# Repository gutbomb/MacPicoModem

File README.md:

# Mac Pico Modem

## A Pico W based RS422 \<-\> WiFi modem with Hayes AT style commands and Global Village Teleport style LED indicators

| The Mac Pico modem |

This project is an adaptation of the [mecparts](https://github.com/mecparts)'s 
[Pico WiFi Modem](https://github.com/mecparts/PicoWiFiModem). 

My goal was to make it work with a mac serial port, look the part, and be
cheaper to make.

### First time setup

The default serial configuration is 9600bps, 8 data bits, no parity, 1
stop bit.

Here's the commands you need to set up the modem to automatically
connect to your WiFi network:

1. `AT$SSID=your WiFi network name` to set the WiFi network that the
modem will connect to when it powers up.
2. `AT$PASS=your WiFi network password` to set the password for the
network.
3. `ATC1` to connect to the network.
4. Optional stuff:
   * `AT$SB=speed` to set the default serial speed.
   * `AT$SU=dps` to set the data bits, parity and stop bits.
   * `ATNETn` to select whether or not to use Telnet protocol.
   * `AT&Kn` to use RTS/CTS flow control or not.
   * `AT&Dn` to set up DTR handling.
5. `AT&W` to save the settings.

Once you've done that, the modem will automatically connect to your WiFi
network on power up and will be ready to "dial up" a connection with
ATDT.

### Command Reference

Multiple AT commands can be typed in on a single line. Spaces between
commands are allowed, but not within commands (i.e. AT S0=1 X1 Q0 is
fine; ATS 0=  1 is not). Commands that take a string as an argument
(e.g. AT$SSID=, AT$TTY=) assume that *everything* that follows is a part
of the string, so no commands are allowed after them.

Command | Details
------- | -------
+++     | Online escape code. Once your modem is connected to another device, the only command it recognises is an escape code of a one second pause followed by three typed plus signs and another one second pause, which puts the modem back into local command mode.
A/      | Repeats the last command entered. Do not type AT or press Enter.
AT      | The attention prefix that precedes all command except A/ and +++.
AT?     | Displays a help cheatsheet.
ATA     | Force the modem to answer an incoming connection when the conditions for auto answer have not been satisfied.
ATC?<br>ATC*n* | Query or change the current WiFi connection status. A result of 0 means that the modem is not connected to WiFi, 1 means the modem is connected. The command ATC0 disconnects the modem from a WiFi connection. ATC1 connects the modem to the WiFi.
ATDS*n* | Calls the host specified in speed dial slot *n* (0-9).
ATDT<i>[+=-]host[:port]</i> | Tries to establish a WiFi TCP connection to the specified host name or IP address. If no port number is given, 23 (Telnet) is assumed. You can also use ATDT to dial one of the speed dial slots in one of two ways:<br><br><ul><li>The alias in each speed dial slot is checked to see if it matches the specified hostname.</li><li>A host specified as 7 identical digits dials the slot indicated by the digit. (i.e. 2222222 would speed dial the host in slot 2).</li></ul>Preceding the host name or IP address with a +, = or - character overrides the ATNET setting for the period of the connection.<br><br><ul><li>**+** forces NET2 (fake Telnet)</li><li>**=** forces NET1 (real Telnet)</li><li>**-** forces NET0 (no Telnet)</li></ul>Once the dial attempt has begun, pressing any key before the connection is established will abort the attempt.
ATE?<br>ATE*n* | Command mode echo. Enables or disables the display of your typed commands.<br><br><ul><li>E0 Command mode echo OFF. Your typing will not appear on the screen.</li><li>E1 Command mode echo ON. Your typing will appear on the screen.</li></ul>
ATGET*http&#58;//host[/page]* | Displays the contents of a website page. **https** connections are not supported. Once the contents have been displayed, the connection will automatically terminate.
ATH | Hangs up (ends) the current connection.
ATI | Displays the current network status, including sketch build date, WiFi and call connection state, SSID name, IP address, and bytes transferred.
ATNET?<br>ATNET*n* | Query or change whether telnet protocol is enabled. A result of 0 means that telnet protocol is disabled; 1 is *Real* telnet protocol and 2 is *Fake* telnet protocol. If you are connecting to a telnet server, it may expect the modem to respond to various telnet commands, such as terminal name (set with `AT$TTY`), terminal window size (set with `AT$TTS`) or terminal speed. Telnet protocol should be enabled for these sites, or you will at best see occasional garbage characters on your screen, or at worst the connection may fail.<br><br>The difference between *real* and *fake* telnet protocol is this: with *real* telnet protocol, a carriage return (CR) character being sent from the modem to the telnet server always has a NUL character added after it. The implementation of the telnet protocol used by some BBSes doesn't properly strip out the NUL character. When connecting to such BBSes (Particles! is one), use *fake* telnet.<br><br>When using *real* telnet protocol, when the telnet server sends a CR character followed by a NUL character, only the CR character will be sent to the serial port; the NUL character will be silently stripped out. With *fake* telnet protocol, the NUL will be passed through.
ATO | Return online. Use with the escape code (+++) to toggle between command and online modes.
ATQ?<br>ATQ*n* | Enable or disable the display of result codes. The default is Q0.<br><br><ul><li>Q0 Display result codes.</li><li>Q1 Suppress result codes (quiet).</li></ul>
ATRD<br>ATRT | Displays the current UTC date and time from NIST in the format *YY-MM-DD HH:MM:SS*. A WiFi connection is required and you cannot be connected to another site.
ATS0?<br>ATS0=*n* | Display or set the number of "rings" before answering an incoming connection. Setting `S0=0` means "don't answer".
ATS2?<br>ATS2=*n* | Display or set the ASCII code used in the online escape sequence. The default value is 43 (the + plus character). Setting it to any value between 128 and 255 will disable the online escape function.
ATV?<br>ATV*n* | Display result codes in words or numbers. The default is V1.<br><br><ul><li>V0 Display result codes in numeric form.</li><li>V1 Display result codes in text form.</li></ul>
ATX?<br>ATX*n* | Control the amount of information displayed in the result codes. The default is X1 (extended codes).<br><br><ul><li>X0 Display basic codes (CONNECT, NO CARRIER)</li><li>X1 Display extended codes (CONNECT speed, NO CARRIER (connect time))</li></ul>
ATZ | Resets the modem.
AT&D?<br>AT&D*n* | Display or set the handling of DTR going inactive. The default is &D0 (ignored).<br><br><ul><li>&D0 Ignore</li><li>&D1 Go to command mode</li><li>&D2 End call</li><li>&D3 Reset modem</li></ul>
AT&F | Reset the NVRAM contents and current settings to the sketch defaults. All settings, including SSID name, password and speed dial slots are affected.
AT&K?<br>AT&K*n* | Data flow control. Prevents the modem's buffers for received and transmitted from overflowing.<br><br><ul><li>&K0 Disable data flow control.</li><li>&K1 Use hardware flow control. Requires that your computer and software support Clear to Send (CTS) and Request to Send (RTS) at the RS-232 interface.</li></ul>
AT&R?<br>AT&R=*server pwd* | Query or change the password for incoming connections. If set, the user has 3 chances in 60 seconds to enter the correct password or the modem will end the connection.
AT&V*n* | Display current or stored settings.<br><br><ul><li>&V0 Display current settings.</li><li>&V1 Display stored settings.</li></ul>
AT&W | Save current settings to NVRAM.
AT&Zn?<br>AT&Z*n*=*host[:port],alias* | Store up to 10 numbers in NVRAM, where *n* is the position 0-9 in NVRAM, and *host[:port]* is the host string, and *alias* is the speed dial alias name. The host string may be up to 50 characters long, and the alias string may be up to 16 characters long.<br><br>Example: `AT&Z2=particlesbbs.dyndns.org:6400,particles`<br><br>This number can then be dialed in any of the following ways:<br><br><ul><li>`ATDS2`</li><li>`ATDTparticles`</li><li>`ATDT2222222`</li></ul>
AT$AE?<br>AT$AE=*startup AT cmd* | Query or change the command line to be executed when the modem starts up.
AT$AYT | Sends a Telnet "Are You There?" command if connected to a Telnet remote.
AT$BM?<br>AT$BM=*server busy msg* | Query or change a message to be returned to an incoming connection if the modem is busy (i.e. already has a connection established).
AT$MDNS<br>AT$MDNS=*mDNS name* | Query or change the mDNS network name (defaults to "espmodem"). When a non zero TCP port is defined, you can telnet to that port with **telnet mdnsname.local port**.
AT$PASS?<br>AT$PASS=*WiFi pwd* | Query or change the current WiFi password. The password is case sensitive. Clear the password by issuing the set command with no password. The maximum length of the password is 64 characters.
AT$SB?<br>AT$SB=*n* | Query or change the current baud rate. Valid values for "n" are 110, 300, 450, 600, 710, 1200, 2400, 4800, 9600, 19200, 38400, 57600, 76800 and 115200. Any other value will return an ERROR message. The default baud rate is 1200. The Pico WiFi modem does not automatically detect baud rate like a dial-up modem. The baud rate setting must match that of your terminal to operate properly. It will display garbage in your terminal otherwise.
AT$SP?<br>AT$SP=*n* | TCP server port to listen on. A value of 0 means that the TCP server is disabled, and no incoming connections are allowed.
AT$SSID?<br>AT$SSID=*ssid name* | Query or change the current SSID to the specified name. The given SSID name is case sensitive. Clear the SSID by issuing the set command with no SSID. The maximum length of the SSID name is 32 characters.
AT$SU?<br>AT$SU=*dps* | Query or change the current number of data bits ('d'), parity ('p') and stop bits ('s") of the serial UART. Valid values for 'd' are 5, 6, 7 or 8 bits. Valid values for 'p' are (N)one, (O)dd or (E)ven parity. Valid values for 's' are 1 or 2 bits. The default settings are 8N1. The UART setting must match your terminal to work properly.
AT$TTL?<br>AT$TTL=*telnet location* | Query or change the Telnet location value to be returned when the Telnet server issues a SEND-LOCATION request. The default value is "Computer Room".
AT$TTS?<br>AT$TTS=*WxH* | Query or change the window size (columns x rows) to be returned when the Telnet server issues a NAWS (Negotiate About Window Size) request. The default value is 80x24. For terminals that are smaller than 80x24, setting these values appropriately will enable paging on the help (AT?) and network status (ATI) commands.
AT$TTY?<br>AT$TTY=*terminal type* | Query or change the terminal type to be returned when the Telnet server issues a TERMINAL-TYPE request. The default value is "ansi".
AT$W?<br>AT$W=*n* | Startup wait.<br><br><ul><li>$W=0 Startup with no wait.</li><li>$W=1 Wait for the return key to be pressed at startup.</li></ul>

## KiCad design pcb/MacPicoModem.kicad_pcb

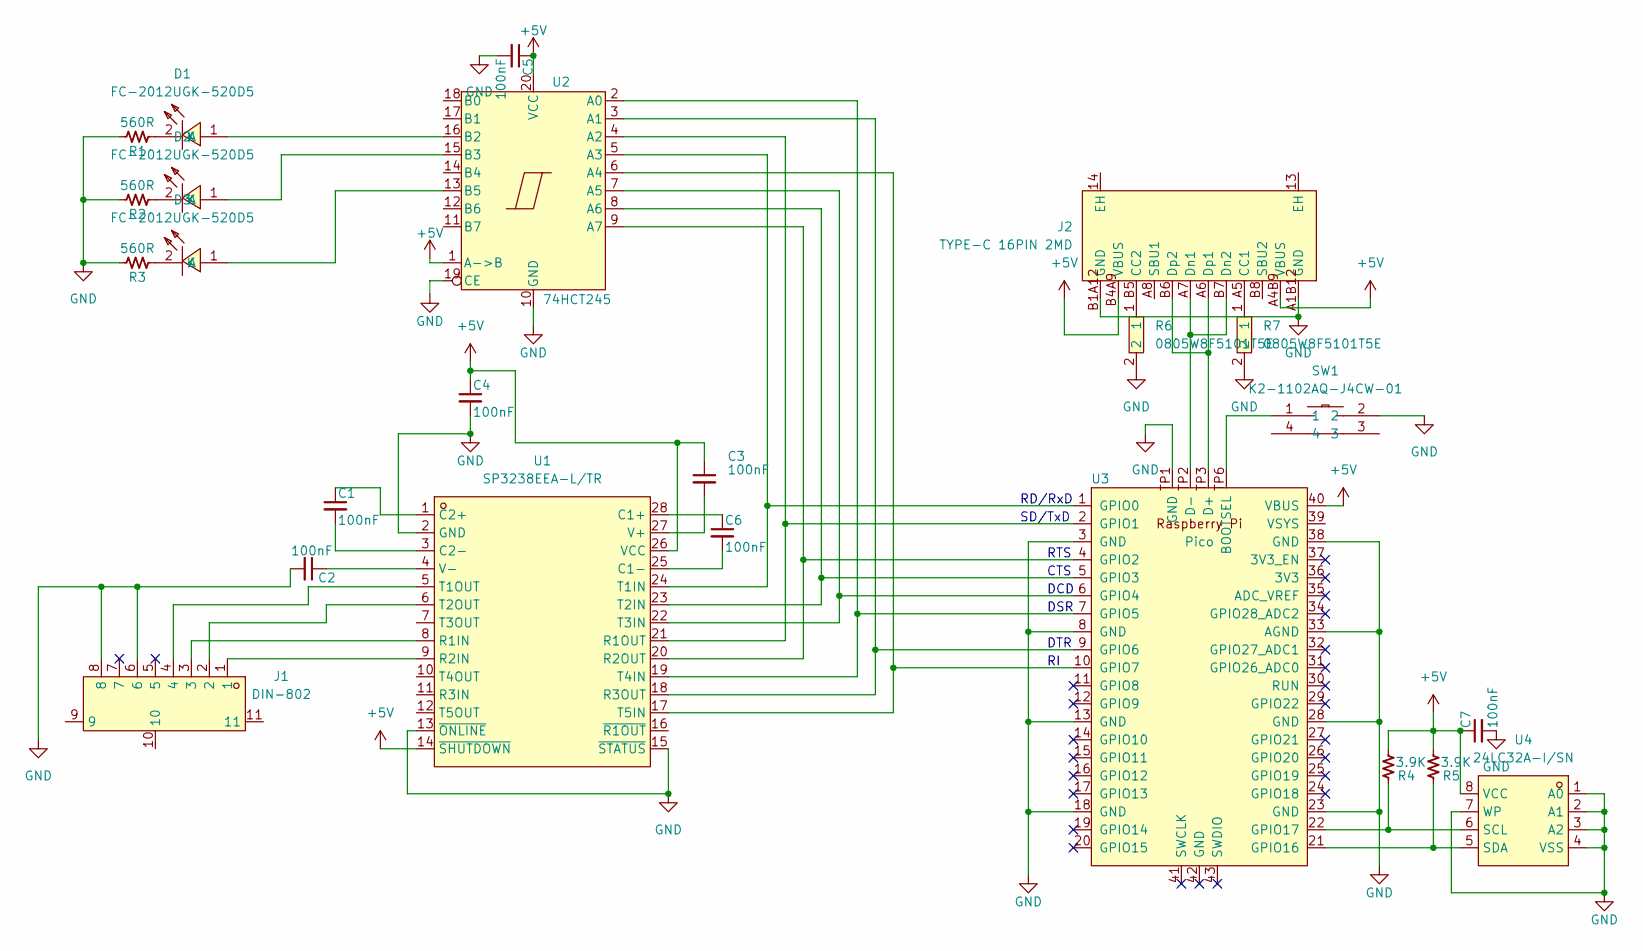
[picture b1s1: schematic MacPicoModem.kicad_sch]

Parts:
C1, C2, C3, C4, C5: 100nF; C_0805_2012Metric; DigiKey PN 399-9859-1-ND
C6, C7: 100nF; C_0805_2012Metric; DigiKey PN 399-9843-ND
D1, D2, D3: FC-2012UGK-520D5; LED0805-R-RD; MPN NCD0805G1; LCSC Part C84260
J1: DIN-802; CONN-TH_DIN-802; MPN DIN-802; LCSC Part C20611694
J2: TYPE-C 16PIN 2MD; USB-C-SMD_TYPE-C-16PIN-2MD-073; MPN TYPE-C 16PIN 2MD(073); LCSC Part C2765186
R1, R2, R3: 560R; R_0805_2012Metric; DigiKey PN CF18JT560RCT-ND
R4, R5: 3.9K; R_0805_2012Metric; LCSC Part C2907252
R6, R7: 0805W8F5101T5E; R0805; MPN 0805W8F5101T5E; LCSC Part C27834
SW1: K2-1102AQ-J4CW-01; KEY-TH_K2-1102AQ-JXXW-XX; MPN K2-1102AQ-J4CW-01; LCSC Part C136735
U1: SP3238EEA-L/TR; SSOP-28_L10.2-W5.3-P0.65-LS7.8-BL; MPN SP3238EEA-L/TR; LCSC Part C49669
U2: 74HCT245; TSSOP-20_L6.5-W4.4-P0.65-LS6.4-BL; LCSC Part C52140501
U3: Pico; RaspberryPi_Pico_W_SMD
U4: 24LC32A-I/SN; SOIC-8_L4.9-W3.9-P1.27-LS6.0-BL; MPN 24LC32A-I/SN; LCSC Part C511262

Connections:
+5V: C3.1, C4.1, C5.1, C7.1, J2.A4B9 (VBUS), J2.B4A9 (VBUS), R4.1, R5.1, U1.14 (~SHUTDOWN), U1.26 (VCC), U2.1 (A->B), U2.20 (VCC), U3.40 (VBUS), U4.8 (VCC)
GND: C2.2, C4.2, C5.2, C7.2, J1.6, J1.8, J2.A1B12 (GND), J2.B1A12 (GND), R1.2, R2.2, R3.2, R6.2, R7.2, SW1.2, U1.2 (GND), U1.13 (~ONLINE), U1.15 (~STATUS), U2.10 (GND), U2.19 (CE), U3.3 (GND), U3.8 (GND), U3.13 (GND), U3.18 (GND), U3.23 (GND), U3.28 (GND), U3.33 (AGND), U3.38 (GND), U3.TP1 (GND), U4.1 (A0), U4.2 (A1), U4.3 (A2), U4.4 (VSS), U4.7 (WP)
unnamed: D1.1 (A), U2.16 (B2)
unnamed: D1.2 (K), R1.1
unnamed: D2.1 (A), U2.15 (B3)
unnamed: D2.2 (K), R2.1
unnamed: D3.1 (A), U2.13 (B5)
unnamed: D3.2 (K), R3.1
unnamed: J2.A5 (CC1), R7.1
unnamed: J2.B5 (CC2), R6.1
unnamed: J2.A7 (Dn1), J2.B7 (Dn2), U3.TP2 (D-)
unnamed: J2.A6 (Dp1), J2.B6 (Dp2), U3.TP3 (D+)
unnamed: C6.1, U1.28 (C1+)
unnamed: C6.2, U1.25 (C1-)
unnamed: C1.1, U1.1 (C2+)
unnamed: C1.2, U1.3 (C2-)
unnamed: J1.3, U1.8 (R1IN)
unnamed: U1.21 (R1OUT), U2.4 (A2), U3.2 (GPIO1)
unnamed: J1.1, U1.9 (R2IN)
unnamed: U1.20 (R2OUT), U2.9 (A7), U3.4 (GPIO2)
unnamed: U1.18 (R3OUT), U2.3 (A1), U3.9 (GPIO6)
unnamed: U1.24 (T1IN), U2.5 (A3), U3.1 (GPIO0)
unnamed: J1.4, U1.5 (T1OUT)
unnamed: U1.23 (T2IN), U2.8 (A6), U3.5 (GPIO3)
unnamed: J1.2, U1.6 (T2OUT)
unnamed: U1.22 (T3IN), U2.7 (A5), U3.6 (GPIO4)
unnamed: U1.19 (T4IN), U2.2 (A0), U3.7 (GPIO5)
unnamed: U1.17 (T5IN), U2.6 (A4), U3.10 (GPIO7)
unnamed: C3.2, U1.27 (V+)
unnamed: C2.1, U1.4 (V-)
unnamed: SW1.1, U3.TP6 (BOOTSEL)
unnamed: R5.2, U3.21 (GPIO16), U4.5 (SDA)
unnamed: R4.2, U3.22 (GPIO17), U4.6 (SCL)

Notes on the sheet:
DTR
RD/RxD
DSR
DCD
RTS
SD/TxD
CTS

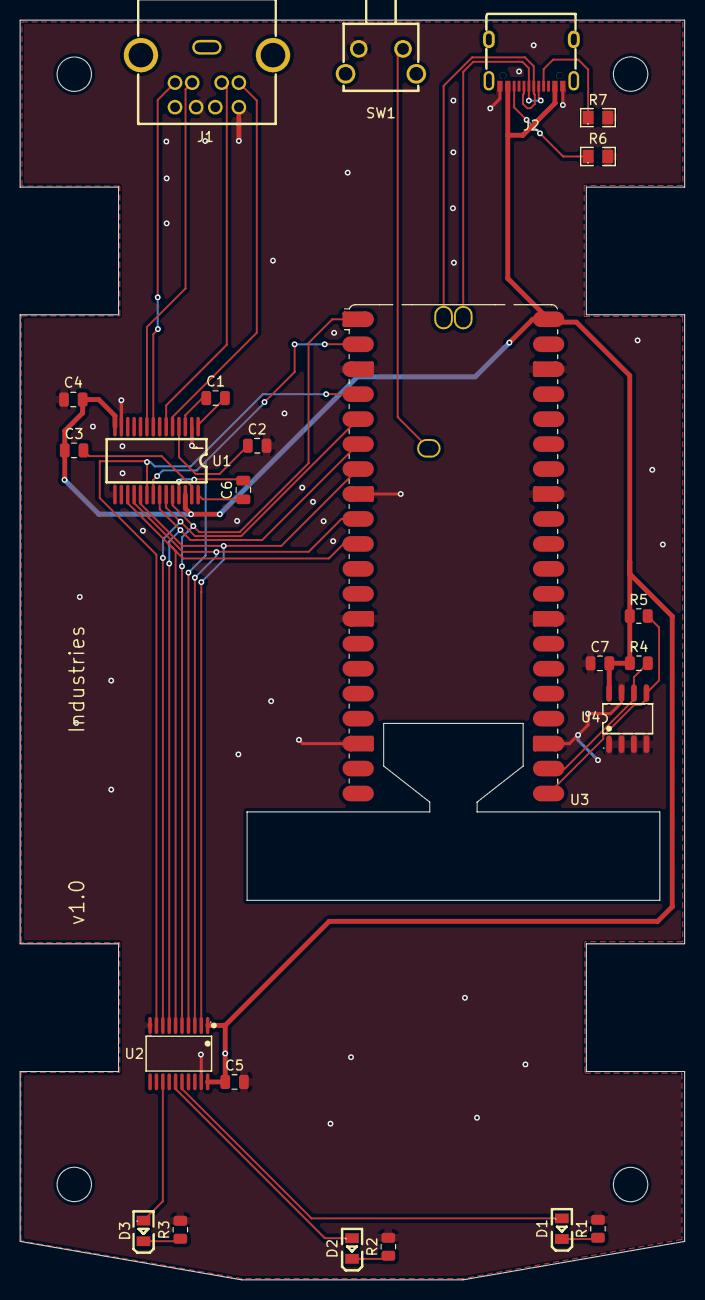
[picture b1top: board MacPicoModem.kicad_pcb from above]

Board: 2 copper layers, 67.6 x 128.2 mm, 24 parts (0 on the bottom side), 33 nets.
